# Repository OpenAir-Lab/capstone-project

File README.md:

<h1 align="center">
<<<<<<< HEAD
  <a href="https://github.com/OpenAir-Lab/capstone-project">
    
=======
  <a href="https://github.com/GITHUB_USERNAME/REPO_SLUG">
    
>>>>>>> 1358599 (docs: organized REV A and REV B pcb and schematic files and put them into their relavent folders)
  </a>
</h1>

<div align="center">
  OpenAir Lab – Modular Handheld Radio Development Kit  
  <br />
  <a href="#about"><strong>Explore the project »</strong></a>
  <br /><br />
<<<<<<< HEAD
  <a href="https://github.com/OpenAir-Lab/capstone-project/issues/new?labels=bug&template=01_BUG_REPORT.md&title=bug%3A+">Report a Bug</a>
  ·
  <a href="https://github.com/OpenAir-Lab/capstone-project/issues/new?labels=enhancement&template=02_FEATURE_REQUEST.md&title=feat%3A+">Request a Feature</a>
  ·
  <a href="https://github.com/OpenAir-Lab/capstone-project/issues/new?labels=question&template=04_SUPPORT_QUESTION.md&title=support%3A+">Ask a Question</a>
=======
  <a href="https://github.com/GITHUB_USERNAME/REPO_SLUG/issues/new?labels=bug&template=01_BUG_REPORT.md&title=bug%3A+">Report a Bug</a>
  ·
  <a href="https://github.com/GITHUB_USERNAME/REPO_SLUG/issues/new?labels=enhancement&template=02_FEATURE_REQUEST.md&title=feat%3A+">Request a Feature</a>
  ·
  <a href="https://github.com/GITHUB_USERNAME/REPO_SLUG/issues/new?labels=question&template=04_SUPPORT_QUESTION.md&title=support%3A+">Ask a Question</a>
>>>>>>> 1358599 (docs: organized REV A and REV B pcb and schematic files and put them into their relavent folders)
</div>

<div align="center">

<<<<<<< HEAD

=======

>>>>>>> 1358599 (docs: organized REV A and REV B pcb and schematic files and put them into their relavent folders)

</div>

---

## **About**

OpenAir Lab is an **open-source, modular handheld ham-radio development kit** designed to expose and teach all fundamental subsystems of a portable transceiver. Unlike commercial “black-box” radios, this platform separates RF, MCU, audio, power, and HMI into independent **Modulinos** connected through standardized EYESPI and I²C interfaces.

<<<<<<< HEAD
The system’s core is an **ESP32-WROVER-E** MCU hosting RF control, audio streaming, display driving, and power-management logic. 

Subsystems include:

- **RF modulino:** TI CC1200 sub-GHz transceiver  

- **HMI modulino:** 1.9" ST7789 TFT via EYESPI, keypad, user buttons, rotary encoder  

- **Audio modulino:** ICS-43434 digital MEMS microphone + MAX98357A I²S amplifier 

- **Power modulino:** STUSB4500 USB-PD, BQ25622 charger, fuel gauge  

- **Control plane:** I²C expander for low-rate signals (LEDs, keypad, resets, alerts)

=======
The system’s core is an **ESP32-WROVER-E** MCU hosting RF control, audio streaming, display driving, and power-management logic. Subsystems include:

- **RF modulino:** TI CC1200 sub-GHz transceiver  
- **HMI modulino:** 1.9" ST7789 TFT via EYESPI, keypad, user buttons, rotary encoder  
- **Audio modulino:** ICS-43434 digital MEMS microphone + MAX98357A I²S amplifier  
- **Power modulino:** STUSB4500 USB-PD, BQ25620 charger, fuel gauge  
- **Control plane:** I²C expander for low-rate signals (LEDs, keypad, resets, alerts)

>>>>>>> 1358599 (docs: organized REV A and REV B pcb and schematic files and put them into their relavent folders)
Purpose:  
• Provide a hands-on educational platform for embedded, RF, and systems engineering  
• Enable modular experimentation and rapid firmware iteration  
• Deliver a working open-source handheld radio for expo demonstration  

---

### **Built With**

- **ESP32-WROVER-E** (dual-core 240 MHz, Wi-Fi/BT, PSRAM)
- **CC1200 Sub-GHz RF Transceiver**  
- **Adafruit 1.9" ST7789 TFT Display + EYESPI connector**  
- **ICS-43434 MEMS microphone**  
- **MAX98357A I²S amplifier**  
- **STUSB4500 USB-PD controller**  
- **BQ25620 battery management IC**  
- **I²C GPIO Expander (TCA9539/MCP23017)**  
- **FreeRTOS-style firmware architecture** (timers, ISRs, tasks)

---

## **Getting Started**

### **Prerequisites**

The project requires:

- ESP32 toolchain (ESP-IDF or PlatformIO/Arduino)
- EYESPI breakout for the TFT display (18-pin FPC)
- Access to I²C and SPI buses for CC1200, audio, and PD controller  
- 3.3 V power supply capable of ≥500 mA for ESP32-WROVER-E  

### **Installation**

1. Clone the repository  
2. Open the firmware directory in ESP-IDF or PlatformIO  
3. Connect the MCU modulino to UART (use BOOT/EN buttons on custom boards)  
4. Build and flash the firmware  
5. Connect modulinos via EYESPI and I²C cables  

---

## **Usage**

Firmware operates through **interrupt-driven inputs**, **FreeRTOS tasks**, and **timers**:

- Keypad, encoder, and PTT interrupts update application state  
- CC1200 provides frequency control, RX/TX switching, and RSSI sampling  
- TFT displays live frequency, signal strength, battery state, settings  
- Tasks handle display refresh, PTT timeout, and periodic battery polling  
- Audio subsystem processes microphone data and sends I²S audio to amplifier  

---

## **Roadmap**

See open issues:  
<<<<<<< HEAD
https://github.com/OpenAir-Lab/capstone-project/issues
=======
https://github.com/GITHUB_USERNAME/REPO_SLUG/issues
>>>>>>> 1358599 (docs: organized REV A and REV B pcb and schematic files and put them into their relavent folders)

Current priorities:

- Finalize pin mapping across all modulinos  
- Complete MCU subsystem schematic in KiCad  
- Implement full FreeRTOS task architecture  
- Bring-up and test Rev A PCB  
- Assemble proof-of-concept handheld radio for expo  

---

## **Support**

Contact the maintainers via:

- GitHub issues (for questions):  
<<<<<<< HEAD
  https://github.com/OpenAir-Lab/capstone-project/issues/new?labels=question  
=======
  https://github.com/GITHUB_USERNAME/REPO_SLUG/issues/new?labels=question  
>>>>>>> 1358599 (docs: organized REV A and REV B pcb and schematic files and put them into their relavent folders)
- Maintainer contact info on GitHub profile  

---

## **Project Assistance**

If you want to support the project:

- Star the repo ⭐  
- Share the project  
- Contribute hardware, firmware, or documentation improvements  

---

## **Contributing**

Contributions are welcome!  
<<<<<<< HEAD
Please review `Documentation/Contributing.md` before submitting a pull request.
=======
Please review `docs/CONTRIBUTING.md` before submitting a pull request.
>>>>>>> 1358599 (docs: organized REV A and REV B pcb and schematic files and put them into their relavent folders)

---

## **Authors & Contributors**

Project created and maintained by the OpenAir Lab MCU & Systems Integration Team.  
Full contributor list:  
<<<<<<< HEAD
https://github.com/OpenAir-Lab/capstone-project/contributors
=======
https://github.com/GITHUB_USERNAME/REPO_SLUG/contributors
>>>>>>> 1358599 (docs: organized REV A and REV B pcb and schematic files and put them into their relavent folders)

---

## **Security**

Provided “as is” with no warranty.  
See `docs/SECURITY.md` for disclosure instructions.

---

## **License**

Licensed under the **MIT License**.  
See `LICENSE` for details.

---

## **Acknowledgements**

This project uses or references:

- **Espressif – ESP32-WROVER-E Datasheet & Technical Reference Manual**  
- **Adafruit – ST7789 TFT & EYESPI Documentation**  
- **Texas Instruments – CC1200 RF Transceiver**  
- **STMicroelectronics – STUSB4500 USB-PD Controller**  
- **TDK/Knowles – ICS-43434 MEMS Microphone**  
- **MAX98357A I²S Amplifier Datasheet**

We also acknowledge the design documentation for the OpenAir Lab subsystem interface and pin mapping.

---

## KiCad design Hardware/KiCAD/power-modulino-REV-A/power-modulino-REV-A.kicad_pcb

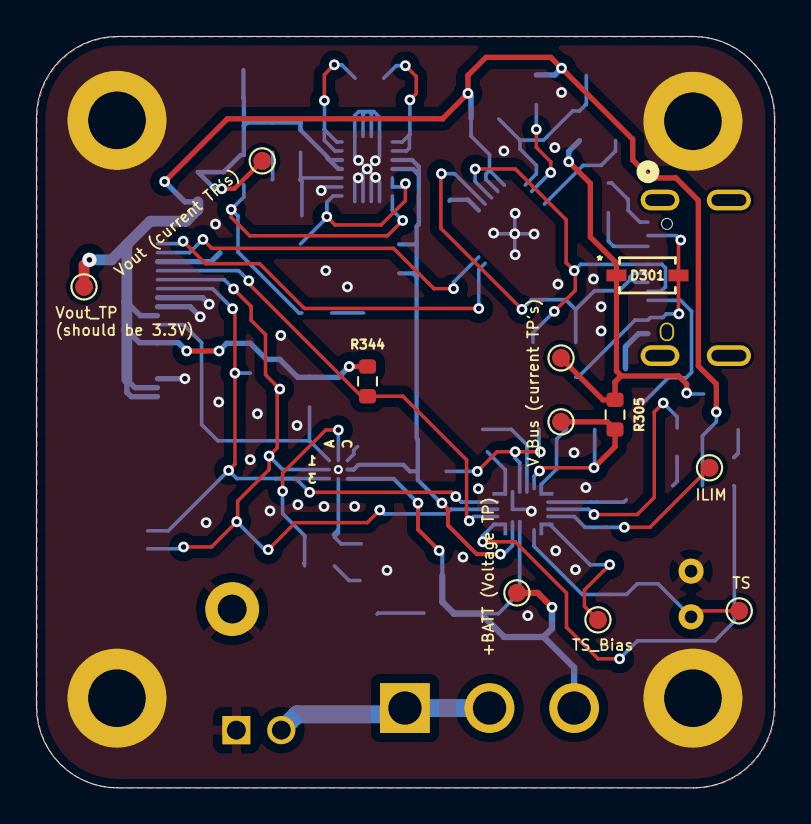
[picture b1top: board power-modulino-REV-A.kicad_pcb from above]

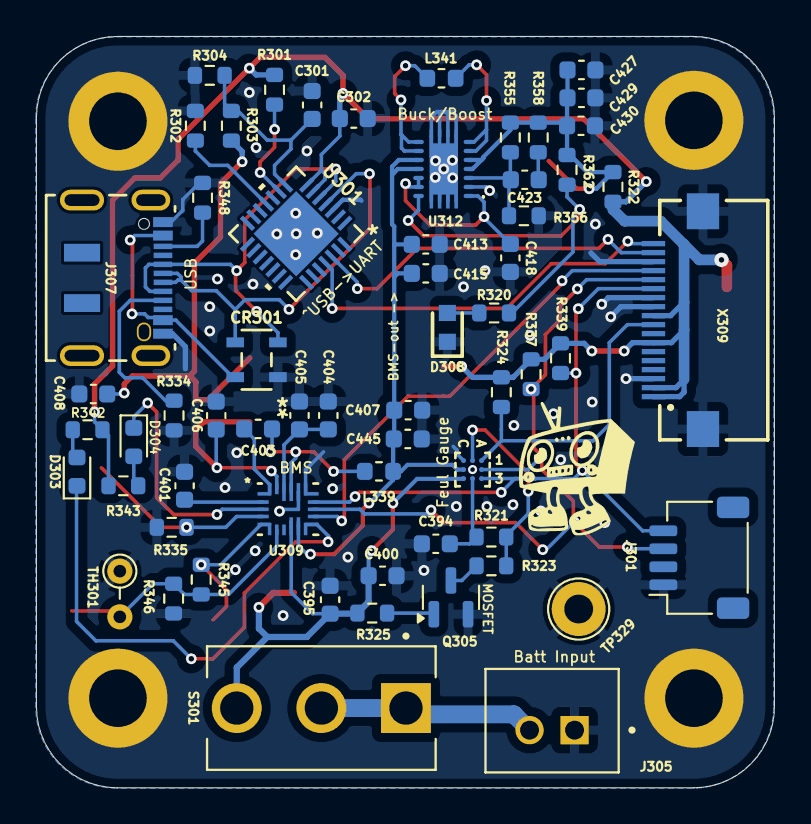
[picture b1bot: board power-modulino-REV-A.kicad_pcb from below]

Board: 2 copper layers, 41.0 x 41.7 mm, 76 parts (65 on the bottom side), 44 nets.

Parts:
C301, C395, C406, C445: 1uF; C_0603_1608Metric
C302, C405: 10uF; C_0603_1608Metric
C394: 2.2uF; C_0603_1608Metric
C400: 10uf; C_0603_1608Metric
C401: 4.7uF; C_0603_1608Metric
C403: 47nF; C_0603_1608Metric
C404: 0.1uF; C_0603_1608Metric
C407: 20uF; C_0603_1608Metric
C408: 4.7u; C_0603_1608Metric
C413, C415: 10u; C_0603_1608Metric
C418: 100n; C_0603_1608Metric
C423: C; C_0603_1608Metric
C427, C429, C430: 22u; C_0603_1608Metric
CR301: SP0503BAHTG; TVS-SP05_LTF
D301: 1N4148WT; 1N5819HW-7-F_DIO
D303, D304: LED; LED_0603_1608Metric
D308: LED; LTST-C190KRKT
H305, H306, H307, H308: MountHole; MountingHole_3.2mm_M3_ISO14580_Pad
J301: Stemma QT; JST_SH_SM04B-SRSS-TB_1x04-1MP_P1.00mm_Horizontal
J305: B2B-XH-A; JST_B2B-XH-A
J307: DX07S016JA1R1500; CONN12_016JA1R1500_JAE
L339: 1uH; L_0603_1608Metric
L341: L; L_0603_1608Metric
Q305: 2N7002; SOT-23
R301: 1K; R_0603_1608Metric
R302, R323, R324, R337, R339, R342, R343, R344: 10k; R_0603_1608Metric
R303: 22.1K; R_0603_1608Metric
R304: 47.5K; R_0603_1608Metric
R305: 0.01; R_0603_1608Metric
R320: 1k; R_0603_1608Metric
R321: 1.8M; R_0603_1608Metric
R322: 0; R_0603_1608Metric
R325: tbd; R_0603_1608Metric
R334, R348: 5.1k; R_0603_1608Metric
R335: TBD; R_0603_1608Metric
R345, R346, R355, R356, R358, R362: R; R_0603_1608Metric
S301: 100SP1T1B4M2QE; SW_100SP1T1B4M2QE
TH301: Thermistor_NTC; R_Axial_DIN0204_L3.6mm_D1.6mm_P2.54mm_Vertical
TP323, TP324, TP326, TP327, TP334, TP335, TP337, TP338: TestPoint; TestPoint_Pad_D1.0mm
TP329: TestPoint; TestPoint_Loop_D2.60mm_Drill1.6mm_Beaded
U301: CP2102N-A02-GQFN28; QFN28_5X5_SIL
U308: BQ27427YZFR; DSBGA9-YZF_TEX
U309: BQ25622RYKR; WQFN-HR18__RYK_TEX
U312: TPS63020QDSJRQ1; TPS63020DSJR
X309: EYESPI; Adafruit EYESPI FPC Connector

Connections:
+3.3V: C302.2, R301.2, R322.1, R324.1, R337.2, R339.2, R342.2, R343.2, R344.2, TP324.1, U301.6 (VDD), U301.7 (VREGIN), X309.1, X309.2, X309.7, X309.10
+BATT: C395.1, C400.1, R325.2, S301.3, TP334.1, U308.C3 (BAT), U309.8 (BAT)
/Power Subsystem/*INT: R344.1, U309.11 (*INT), X309.15
/Power Subsystem/*PG: D304.1 (K), U309.3 (*PG)
/Power Subsystem/BMS_out: C407.2, C413.1, C415.1, C445.2, L339.2, U308.C2 (SRX), U309.9 (SYS), U312.10 (VIN_1), U312.11 (VIN_2)
/Power Subsystem/D+: CR301.3, J307.6 (D+), J307.7 (D+__1), U301.4 (D+)
/Power Subsystem/D-: CR301.2, J307.5 (D-), J307.8 (D-__1), U301.5 (D-)
/Power Subsystem/ILIM: R335.2, TP337.1, U309.4 (ILIM)
/Power Subsystem/RXD: U301.25 (RXD), X309.18
/Power Subsystem/SCL: J301.4, R339.1, U308.A3 (SCL), U309.13 (SCL), X309.13
/Power Subsystem/SDA: J301.3, R337.1, U308.A2 (SDA), U309.12 (SDA), X309.14
/Power Subsystem/STAT: D303.1 (K), U309.10 (STAT)
/Power Subsystem/TS: R345.2, R346.1, TH301.2, TP338.1, U309.6 (TS)
/Power Subsystem/TS_BIAS: R345.1, TP335.1, U309.5 (TS_BIAS)
/Power Subsystem/TXD: U301.26 (TXD), X309.17
/Power Subsystem/VDD: C394.1, R321.2, U308.B3 (VDD)
/Power Subsystem/~BAT_INT: R324.2, U308.A1 (GPOUT), X309.9
GND: C301.1, C302.1, C394.2, C395.2, C400.2, C401.1, C404.1, C405.1, C406.1, C407.1, C408.2, C413.2, C415.2, C418.2, C427.2, C429.2, C430.2, C445.1, CR301.1, D308.1 (K), H305.1, H306.1, H307.1, H308.1, J301.1, J305.1, J307.1 (GND), J307.12 (GND__1), Q305.2 (S), R302.2, R304.1, R334.2, R335.1, R346.2, R348.2, R356.1, TH301.1, TP329.1, U301.3 (GND), U301.29 (GND), U308.B2 (VSS), U308.C1 (VSS), U309.14 (*CE), U309.15 (GND), U312.2 (GND), U312.15 (PGND_1), U312.16 (GND), U312.17 (GND), U312.18 (GND), U312.19 (GND), U312.20 (GND), U312.21 (GND), U312.22 (GND), U312.23 (GND), X309.3, X309.11, X309.12, X309.16, X309.Z1, X309.Z2
unnamed: C423.1, R358.1
unnamed: CR301.4, D301.2 (A), J307.2 (VBUS), J307.11 (VBUS__1)
unnamed: D303.2 (A), R342.1
unnamed: D304.2 (A), R343.1
unnamed: D308.2 (A), R320.2
unnamed: J305.2, S301.1, S301.2
unnamed: J307.3 (CC1), R348.1
unnamed: J307.9 (CC2), R334.1
unnamed: Q305.3 (D), R323.1
unnamed: Q305.1 (G), R325.1
unnamed: R301.1, U301.9 (RSTb)
unnamed: R302.1, U301.11 (SUSPENDb)
unnamed: C301.2, R303.2, R304.2, U301.8 (VBUS)
unnamed: R321.1, R323.2, U308.B1 (BIN)
unnamed: C403.2, U309.1 (BTST)
unnamed: C404.2, C405.2, U309.17 (PMID)
unnamed: C401.2, U309.2 (REGN)
unnamed: C403.1, L339.1, U309.16 (SW)
unnamed: C406.2, R305.2, TP326.1, U309.18 (VBUS)
unnamed: C418.1, U312.1 (VINA), U312.12 (EN), U312.13 (PS/SYNC)
unnamed: C423.2, R355.1, R356.2, U312.3 (FB)
unnamed: L341.1, U312.8 (L1_1), U312.9 (L1_2)
unnamed: L341.2, U312.6 (L2_1), U312.7 (L2_2)
unnamed: R320.1, R362.1, U312.14 (PG)
unnamed: C427.1, C429.1, C430.1, R322.2, R355.2, R358.2, R362.2, TP323.1, U312.4 (VOUT_1), U312.5 (VOUT_2)
VBUS: C408.1, D301.1 (K), R303.1, R305.1, TP327.1

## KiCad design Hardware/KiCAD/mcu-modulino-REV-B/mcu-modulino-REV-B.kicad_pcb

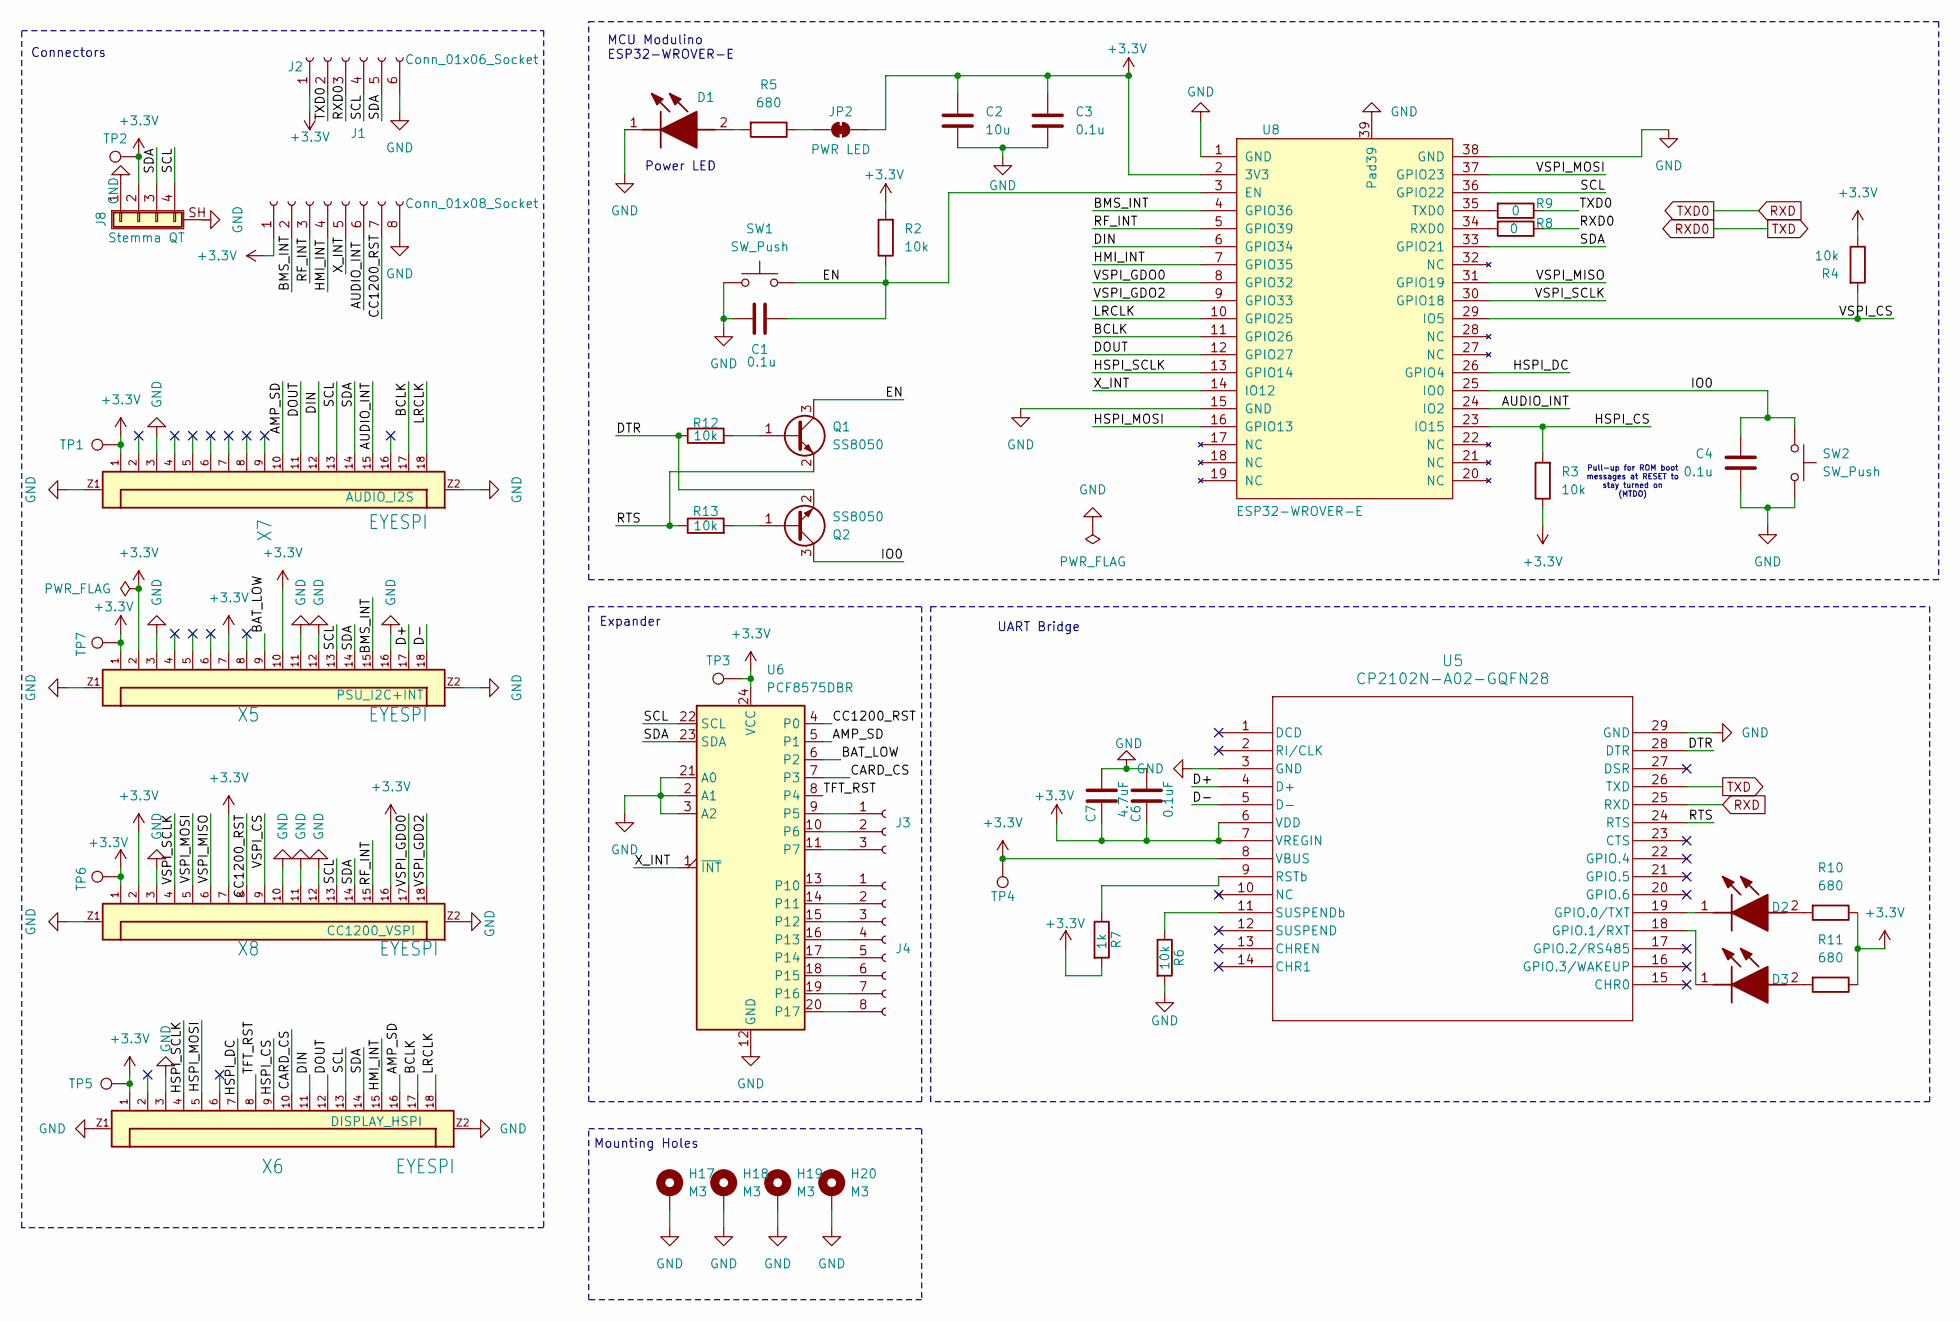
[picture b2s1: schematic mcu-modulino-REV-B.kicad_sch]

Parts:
C1, C3, C4: 0.1u; C_0603_1608Metric
C2: 10u; C_0603_1608Metric
C6: 0.1uF; C_0603_1608Metric
C7: 4.7uF; C_0603_1608Metric
D1: LTST-C190KRKT; LED_0603_1608Metric; Mouser Part Number 859-LTST-C190KRKT
D2, D3: LTST-C191GKT; Mouser Part Number 859-LTST-C191GKT
H17, H18, H19, H20: M3; MountingHole_3.2mm_M3_ISO14580_Pad
J1: Conn_01x08_Socket; PinSocket_1x08_P2.54mm_Vertical
J2: Conn_01x06_Socket; PinHeader_1x06_P1.00mm_Vertical
J3: Conn_01x03_Socket; PinSocket_1x03_P1.27mm_Vertical
J4: Conn_01x08_Socket; PinSocket_1x08_P1.27mm_Vertical
J8: Stemma QT; JST_SH_SM04B-SRSS-TB_1x04-1MP_P1.00mm_Horizontal
JP2: PWR LED; SolderJumper-2_P1.3mm_Bridged_RoundedPad1.0x1.5mm
Q1, Q2: SS8050; SOT-23
R2, R3, R4, R6, R12, R13: 10k; R_0603_1608Metric
R5, R10, R11: 680; R_0603_1608Metric
R7: 1k; R_0603_1608Metric
R8, R9: 0; R_0603_1608Metric
SW1, SW2: SW_Push; SW_SPST_EVQP2_MiddlePushTravel_H2.5mm
TP1, TP2, TP3, TP4, TP5, TP6, TP7: TestPoint; TestPoint_Pad_D1.0mm
U5: CP2102N-A02-GQFN28; QFN28_5X5_SIL
U6: PCF8575DBR; SSOP-24_5.3x8.2mm_P0.65mm
U8: ESP32-WROVER-E; ESP32-WROVER-IE
X5, X6, X7, X8: EYESPI; Adafruit EYESPI FPC Connector

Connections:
+3.3V: C2.1, C3.1, C6.2, C7.2, J2.1, J8.2, JP2.2 (B), R2.2, R3.1, R4.1, R7.2, R10.1, R11.1, TP1.1, TP2.1, TP3.1, TP4.1, TP5.1, TP6.1, TP7.1, U5.6 (VDD), U5.7 (VREGIN), U5.8 (VBUS), U6.24 (VCC), U8.2 (3V3), X5.1, X5.2, X5.7, X5.10, X6.1, X7.1, X8.1, X8.2, X8.7, X8.16
/AMP_SD: U6.5 (P1), X6.16, X7.10
/AUDIO_INT: J1.6, U8.24 (IO2), X7.15
/BAT_LOW: U6.6 (P2), X5.9
/BCLK: U8.11 (GPIO26), X6.17, X7.17
/BMS_INT: U8.4 (GPIO36), X5.15
/CARD_CS: U6.7 (P3), X6.10
/CC1200_RST: U6.4 (P0), X8.8
/D+: U5.4 (D+), X5.17
/D-: U5.5 (D-), X5.18
/DIN: U8.6 (GPIO34), X6.11, X7.12
/DOUT: U8.12 (GPIO27), X6.12, X7.11
/DTR: Q2.2 (E), R12.1, U5.28 (DTR)
/EN: C1.2, Q1.3 (C), R2.1, SW1.2, U8.3 (EN)
/HMI_INT: U8.7 (GPIO35), X6.15
/HSPI_CS: R3.2, U8.23 (IO15), X6.9
/HSPI_DC: U8.26 (GPIO4), X6.7
/HSPI_MOSI: U8.16 (GPIO13), X6.5
/HSPI_SCLK: U8.13 (GPIO14), X6.4
/IO0: C4.1, Q2.3 (C), SW2.1, U8.25 (IO0)
/LRCLK: U8.10 (GPIO25), X6.18, X7.18
/RF_INT: U8.5 (GPIO39), X8.15
/RTS: Q1.2 (E), R13.1, U5.24 (RTS)
/SCL: J2.4, J8.4, U6.22 (SCL), U8.36 (GPIO22), X5.13, X6.13, X7.13, X8.13
/SDA: J2.5, J8.3, U6.23 (SDA), U8.33 (GPIO21), X5.14, X6.14, X7.14, X8.14
/TFT_RST: U6.8 (P4), X6.8
/VSPI_CS: R4.2, U8.29 (IO5), X8.9
/VSPI_GDO0: U8.8 (GPIO32), X8.17
/VSPI_GDO2: U8.9 (GPIO33), X8.18
/VSPI_MISO: U8.31 (GPIO19), X8.6
/VSPI_MOSI: U8.37 (GPIO23), X8.5
/VSPI_SCLK: U8.30 (GPIO18), X8.4
/X_INT: J1.5, U6.1 (~INT), U8.14 (IO12)
GND: C1.1, C2.2, C3.2, C4.2, C6.1, C7.1, D1.1 (K), H18.1, H20.1, J2.6, J8.1, J8.SH (Shield), R6.2, SW1.1, SW2.2, U5.3 (GND), U5.29 (GND), U6.2 (A1), U6.3 (A2), U6.12 (GND), U6.21 (A0), U8.1 (GND), U8.15 (GND), U8.38 (GND), U8.39 (Pad39), X5.3, X5.11, X5.12, X5.16, X5.Z1, X5.Z2, X6.3, X6.Z1, X6.Z2, X7.3, X7.Z1, X7.Z2, X8.3, X8.10, X8.11, X8.12, X8.Z1, X8.Z2
unnamed: D1.2 (A), R5.2
unnamed: D2.2 (A), R10.2
unnamed: D2.1 (K), U5.19 (GPIO.0/TXT)
unnamed: D3.2 (A), R11.2
unnamed: D3.1 (K), U5.18 (GPIO.1/RXT)
unnamed: J3.1, U6.9 (P5)
unnamed: J3.2, U6.10 (P6)
unnamed: J3.3, U6.11 (P7)
unnamed: J4.1, U6.13 (P10)
unnamed: J4.2, U6.14 (P11)
unnamed: J4.3, U6.15 (P12)
unnamed: J4.4, U6.16 (P13)
unnamed: J4.5, U6.17 (P14)
unnamed: J4.6, U6.18 (P15)
unnamed: J4.7, U6.19 (P16)
unnamed: J4.8, U6.20 (P17)
unnamed: JP2.1 (A), R5.1
unnamed: Q1.1 (B), R12.2
unnamed: Q2.1 (B), R13.2
unnamed: R7.1, U5.9 (RSTb)
unnamed: R6.1, U5.11 (SUSPENDb)
unnamed: R8.2, U8.34 (RXD0)
unnamed: R9.2, U8.35 (TXD0)
RXD: J2.2, R9.1, U5.25 (RXD)
RXD0: J2.3, R8.1, U5.26 (TXD)

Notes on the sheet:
UART Bridge
Pull-up for ROM boot messages at RESET to stay turned on (MTDO)
Power LED
Connectors
MCU Modulino ESP32-WROVER-E
Expander
Mounting Holes

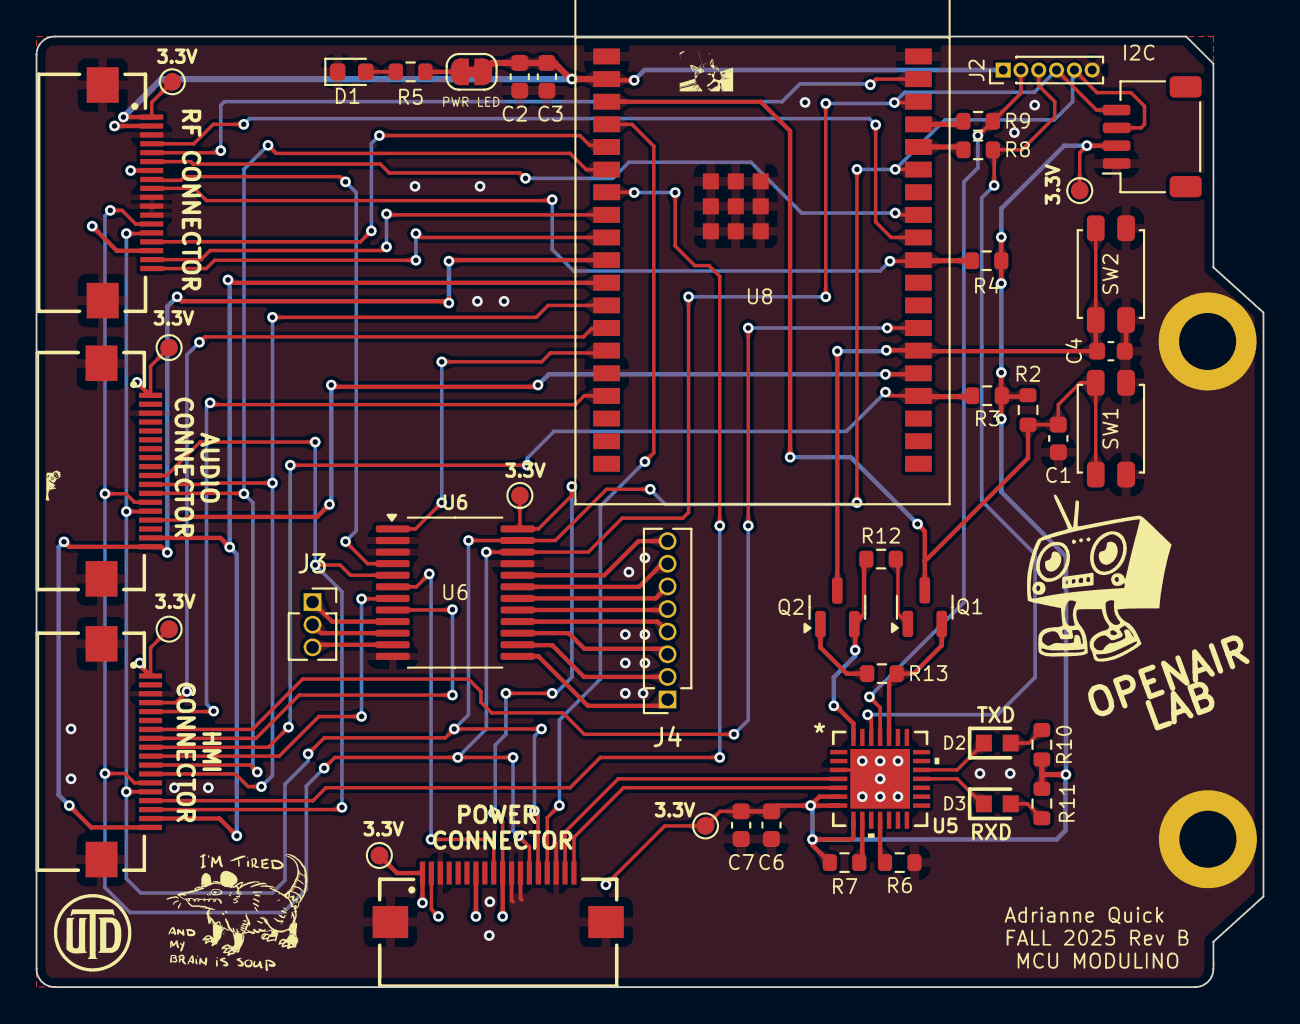
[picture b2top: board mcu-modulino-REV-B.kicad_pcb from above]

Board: 4 copper layers, 68.9 x 53.3 mm, 46 parts (0 on the bottom side), 59 nets.

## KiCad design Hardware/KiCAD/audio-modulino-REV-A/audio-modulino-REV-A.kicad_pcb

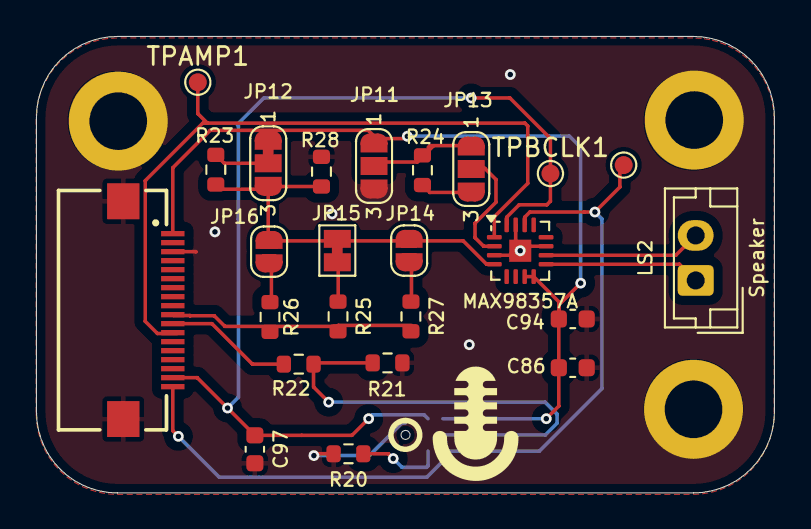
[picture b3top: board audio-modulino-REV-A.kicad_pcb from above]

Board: 2 copper layers, 41.0 x 25.4 mm, 28 parts (1 on the bottom side), 19 nets.

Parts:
C86: 1uF; C_0603_1608Metric
C94: 0.1uF; C_0603_1608Metric
C97: 22pF; C_0603_1608Metric
H13, H15, H16: M3; MountingHole_3.2mm_M3_ISO14580_Pad
JP11: GAIN_{LOGIC}; SolderJumper-3_P1.3mm_Open_RoundedPad1.0x1.5mm_NumberLabels
JP12: Driver; SolderJumper-3_P1.3mm_Bridged12_RoundedPad1.0x1.5mm_NumberL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
JP13: GAIN_{R}; SolderJumper-3_P1.3mm_Open_RoundedPad1.0x1.5mm_NumberLabels
JP14: CH_LEFT; SolderJumper-2_P1.3mm_Open_RoundedPad1.0x1.5mm
JP15: CH_MONO_MIX; SolderJumper-2_P1.3mm_Bridged_Pad1.0x1.5mm
JP16: CH_RIGHT; SolderJumper-2_P1.3mm_Open_RoundedPad1.0x1.5mm
LS2: Speaker; JST_EH_B2B-EH-A_1x02_P2.50mm_Vertical
MK2: ICS-43434; InvenSense_ICS-43434-6_3.5x2.65mm
R20, R21: 47k; R_0603_1608Metric
R22: 68; R_0603_1608Metric
R23, R27: 2k; R_0603_1608Metric
R24: 100k 5%; R_0603_1608Metric
R25: 634k; R_0603_1608Metric
R26: 330k; R_0603_1608Metric
R28: 100k; R_0603_1608Metric
TPAMP1: TestPoint_Pad_D1.0mm
TPBCLK1: TestPoint_Pad_D1.0mm
TPLRCLK1: TestPoint_Pad_D1.0mm
U7: MAX98357A; TQFN-16-1EP_3x3mm_P0.5mm_EP1.23x1.23mm
X2: EYESPI; Adafruit EYESPI FPC Connector

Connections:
+3.3V: C86.1, C94.1, JP11.1 (A), JP12.1 (A), MK2.5 (VDD), U7.7 (VDD), U7.8 (VDD), X2.1
/AMP_DIN: TPAMP1.1, U7.1 (DIN), X2.12
/Audio Subsystem/GAIN_SLOT: JP13.2 (C), U7.2 (GAIN_SLOT)
/Audio Subsystem/~SD_MODE: JP12.3 (B), JP14.2 (B), JP15.2 (B), JP16.2 (B), R23.2, R28.2, U7.4 (~SD_MODE)
/BCLK: C97.1, MK2.4 (SCK), TPBCLK1.1, U7.16 (BCLK), X2.17
/LRCLK: MK2.1 (WS), TPLRCLK1.1, U7.14 (LRCLK), X2.18
/MIC_DOUT: R22.2, X2.11
/~AMP_SD: R25.2, R26.1, R27.2, X2.10
GND: C86.2, C94.2, C97.2, H13.1, H15.1, H16.1, JP11.3 (B), MK2.3 (GND), R20.2, R21.2, R28.1, U7.3 (GND), U7.11 (GND), U7.15 (GND), U7.17 (PAD), X2.3, X2.Z1, X2.Z2
unnamed: JP11.2 (C), JP13.1 (A), R24.1
unnamed: JP12.2 (C), R23.1
unnamed: JP13.3 (B), R24.2
unnamed: JP14.1 (A), R27.1
unnamed: JP15.1 (A), R25.1
unnamed: JP16.1 (A), R26.2
unnamed: MK2.2 (LR), R20.1
unnamed: MK2.6 (SD), R21.1, R22.1
unnamed: LS2.2, U7.10 (OUTN)
unnamed: LS2.1, U7.9 (OUTP)

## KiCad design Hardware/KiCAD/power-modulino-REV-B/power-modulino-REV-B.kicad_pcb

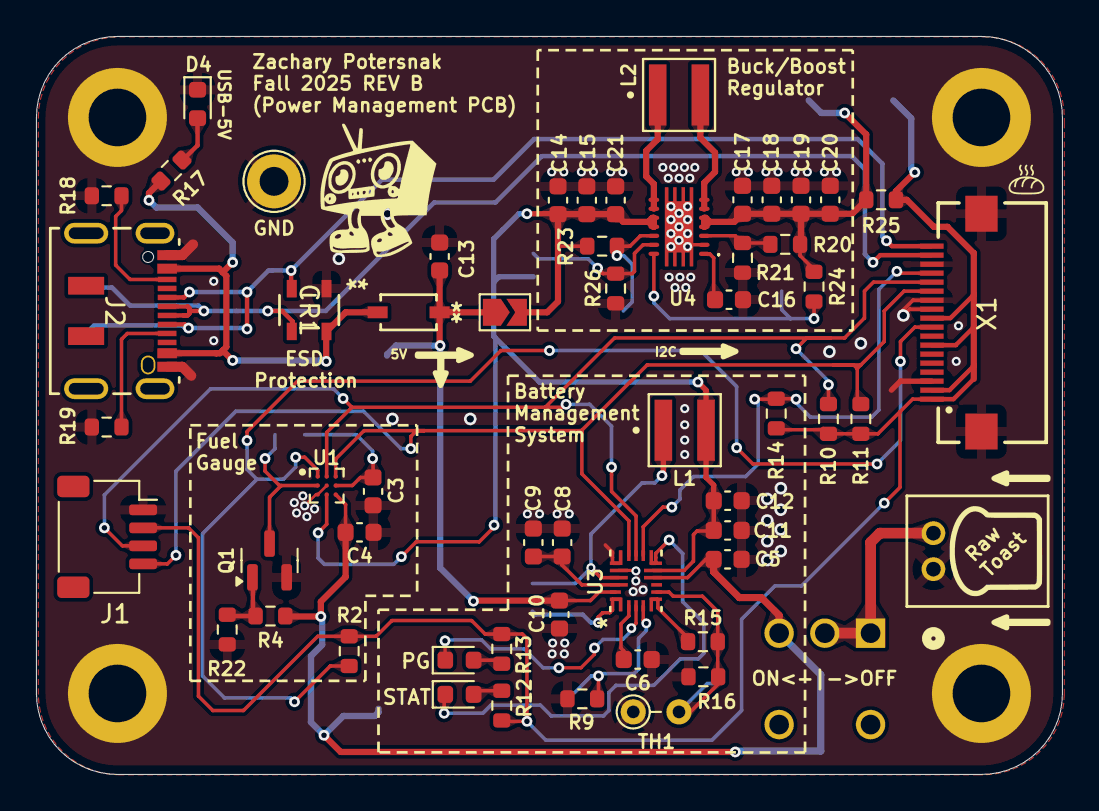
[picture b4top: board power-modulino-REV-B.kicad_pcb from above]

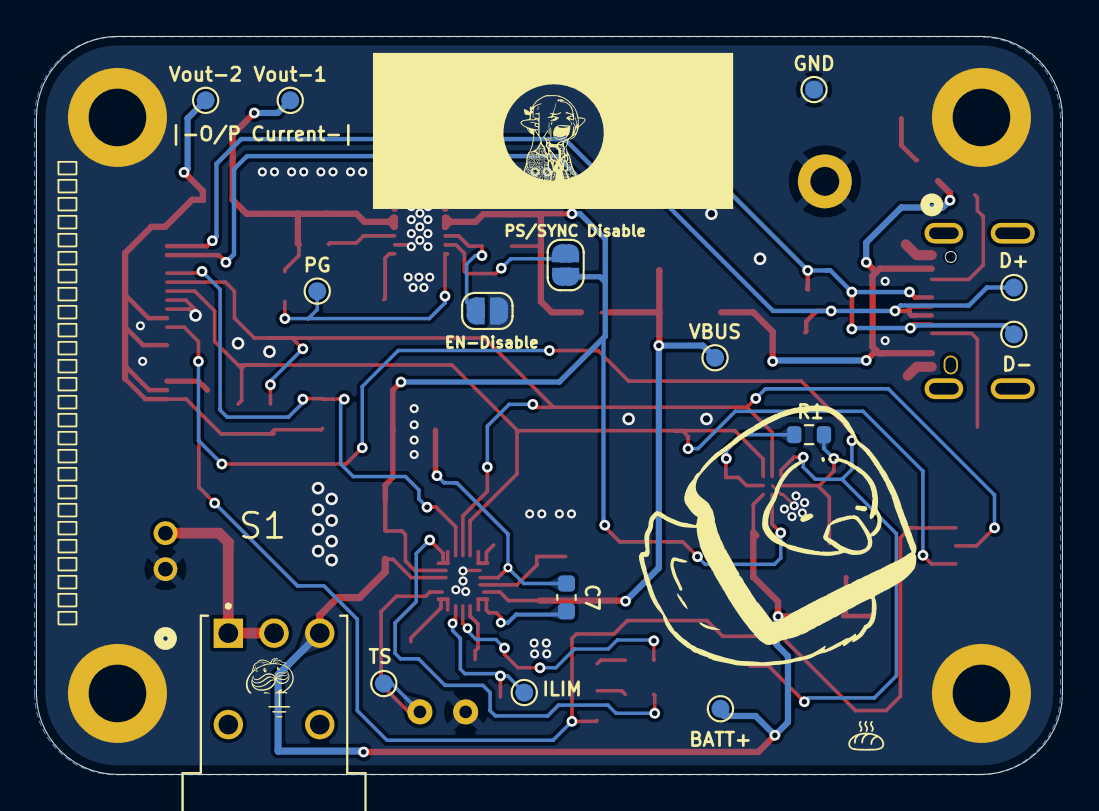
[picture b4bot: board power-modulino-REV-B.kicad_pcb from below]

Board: 2 copper layers, 57.0 x 41.0 mm, 75 parts (15 on the bottom side), 38 nets.

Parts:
BATT+: TestPoint; TestPoint_Pad_D1.0mm
C3: 2.2uF; C_0603_1608Metric
C4, C10, C12: 1uF; C_0603_1608Metric
C5: 10uf; C_0603_1608Metric
C6: 4.7uF; C_0603_1608Metric
C7: 47nF; C_0603_1608Metric
C8: 0.1uF; C_0603_1608Metric
C9: 10uF; C_0603_1608Metric
C11: 20uF; C_0603_1608Metric
C13: 4.7u; C_0603_1608Metric
C14, C15, C18, C19, C20: 22u; C_0603_1608Metric
C16: 100n; C_0603_1608Metric
C17, C21: 2.2u; C_0603_1608Metric
CR1: SP0503BAHTG; TVS-SP05_LTF
D3: 1N4148WT; 1N5819HW-7-F_DIO
D4: LED; LED_0603_1608Metric
D+: TestPoint; TestPoint_Pad_D1.0mm
D-: TestPoint; TestPoint_Pad_D1.0mm
GND: TestPoint; TestPoint_Loop_D2.60mm_Drill1.6mm_Beaded
GND#2: TestPoint; TestPoint_Pad_D1.0mm
H1, H2, H3, H4: MountHole; MountingHole_3.2mm_M3_ISO14580_Pad
ILIM: TestPoint; TestPoint_Pad_D1.0mm
J1: Stemma QT; JST_SH_SM04B-SRSS-TB_1x04-1MP_P1.00mm_Horizontal
J2: DX07S016JA1R1500; CONN12_016JA1R1500_JAE
J3: S2B-PH-K-SLFSN; CONN_S2B-PH-K-S_JST
JP1: SolderJumper_2_Open; SolderJumper-2_P1.3mm_Open_TrianglePad1.0x1.5mm
JP2, JP3: SolderJumper_2_Open; SolderJumper-2_P1.3mm_Open_RoundedPad1.0x1.5mm
L1: 2.2uH; IND_XFL4020-222MEC
L2: 1.5u; IND_XFL4020-222MEC
PG: LED; LED_0603_1608Metric
PG#2: TestPoint; TestPoint_Pad_D1.0mm
Q1: 2N7002; SOT-23
R1: 1.8M; R_0603_1608Metric
R2, R10, R11, R14: 10k; R_0603_1608Metric
R4: 100; R_0603_1608Metric
R9: 1.6k; R_0603_1608Metric
R12, R13: 2.2k; R_0603_1608Metric
R15, R18, R19: 5.1k; R_0603_1608Metric
R16: 30k; R_0603_1608Metric
R17: 1.2K; R_0603_1608Metric
R20, R23, R24, R26: 1M; R_0603_1608Metric
R21: 180k; R_0603_1608Metric
R22: 100K; R_0603_1608Metric
R25: 0; R_0603_1608Metric
S1: 500ASSP1M6QE; SW_500ASSP1M6QE
STAT: LED; LED_0603_1608Metric
TH1: Thermistor_NTC; R_Axial_DIN0204_L3.6mm_D1.6mm_P2.54mm_Vertical
TS: TestPoint; TestPoint_Pad_D1.0mm
U1: BQ27427YZFR; IC_BQ27427YZFR
U3: BQ25622RYKR; WQFN-HR18__RYK_TEX
U4: TPS63020QDSJRQ1; TPS63020DSJR
VBUS: TestPoint; TestPoint_Pad_D1.0mm
Vout-1, Vout-2: TestPoint; TestPoint_Pad_D1.0mm
X1: EYESPI; Adafruit EYESPI FPC Connector

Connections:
+3.3V: J1.2, R2.1, R10.2, R11.2, R12.2, R13.2, R14.2, R25.1, Vout-2.1, X1.1, X1.2, X1.7, X1.10
+5V: C11.2, C12.2, C14.1, C15.1, C21.1, JP1.2 (B), JP3.2 (B), L1.2, R23.1, U1.C2 (SRX), U3.9 (SYS), U4.10 (VIN_1), U4.11 (VIN_2)
+BATT: BATT+.1, C4.1, C5.1, R4.2, S1.3, U1.C3 (BAT), U3.8 (BAT)
/Power Subsystem/*INT: R14.1, U3.11 (*INT), X1.15
/Power Subsystem/*PG: PG.1 (K), U3.3 (*PG)
/Power Subsystem/BAT_LOW: R2.2, U1.A1 (GPOUT), X1.9
/Power Subsystem/D+: CR1.3, D+.1, J2.6 (D+), J2.7 (D+__1), X1.17
/Power Subsystem/D-: CR1.2, D-.1, J2.5 (D-), J2.8 (D-__1), X1.18
/Power Subsystem/ILIM: ILIM.1, R9.2, U3.4 (ILIM)
/Power Subsystem/Regulators/EN: JP2.1 (A), R23.2, U4.12 (EN)
/Power Subsystem/Regulators/PS/SYNC: JP3.1 (A), R26.2, U4.13 (PS/SYNC)
/Power Subsystem/SCL: J1.4, R11.1, U1.A3 (SCL), U3.13 (SCL), X1.13
/Power Subsystem/SDA: J1.3, R10.1, U1.A2 (SDA), U3.12 (SDA), X1.14
/Power Subsystem/STAT: STAT.1 (K), U3.10 (STAT)
/Power Subsystem/TS: R15.2, R16.1, TH1.2, TS.1, U3.6 (TS)
/Power Subsystem/TS_BIAS: R15.1, U3.5 (TS_BIAS)
/Power Subsystem/VDD: C3.1, R1.2, U1.B3 (VDD)
GND: C3.2, C4.2, C5.2, C6.1, C8.1, C9.1, C10.1, C11.1, C12.1, C13.2, C14.2, C15.2, C16.2, C17.2, C18.2, C19.2, C20.2, C21.2, CR1.1, D4.1 (K), GND.1, GND#2.1, H1.1, H2.1, H3.1, H4.1, J1.1, J2.1 (GND), J2.12 (GND__1), J3.1, JP2.2 (B), Q1.2 (S), R9.1, R16.2, R18.2, R19.2, R21.1, R22.2, R26.1, TH1.1, U1.B2 (VSS), U1.C1 (VSS), U3.14 (*CE), U3.15 (GND), U4.2 (GND), U4.15 (PGND_1), X1.3, X1.11, X1.12, X1.16, X1.Z1, X1.Z2
unnamed: R12.1, STAT.2 (A)
unnamed: PG.2 (A), R13.1
unnamed: CR1.4, D3.2 (A), J2.2 (VBUS), J2.11 (VBUS__1), R17.1
unnamed: D4.2 (A), R17.2
unnamed: J2.3 (CC1), R18.1
unnamed: J2.9 (CC2), R19.1
unnamed: J3.2, S1.1, S1.2
unnamed: Q1.3 (D), R1.1, U1.B1 (BIN)
unnamed: Q1.1 (G), R4.1, R22.1
unnamed: C7.2, U3.1 (BTST)
unnamed: C8.2, C9.2, U3.17 (PMID)
unnamed: C6.2, U3.2 (REGN)
unnamed: C7.1, L1.1, U3.16 (SW)
unnamed: R20.1, R21.2, U4.3 (FB)
unnamed: L2.1, U4.8 (L1_1), U4.9 (L1_2)
unnamed: L2.2, U4.6 (L2_1), U4.7 (L2_2)
unnamed: PG#2.1, R24.1, U4.14 (PG)
unnamed: C16.1, U4.1 (VINA)
unnamed: C17.1, C18.1, C19.1, C20.1, R20.2, R24.2, R25.2, U4.4 (VOUT_1), U4.5 (VOUT_2), Vout-1.1
VBUS: C10.2, C13.1, D3.1 (K), JP1.1 (A), U3.18 (VBUS), VBUS.1

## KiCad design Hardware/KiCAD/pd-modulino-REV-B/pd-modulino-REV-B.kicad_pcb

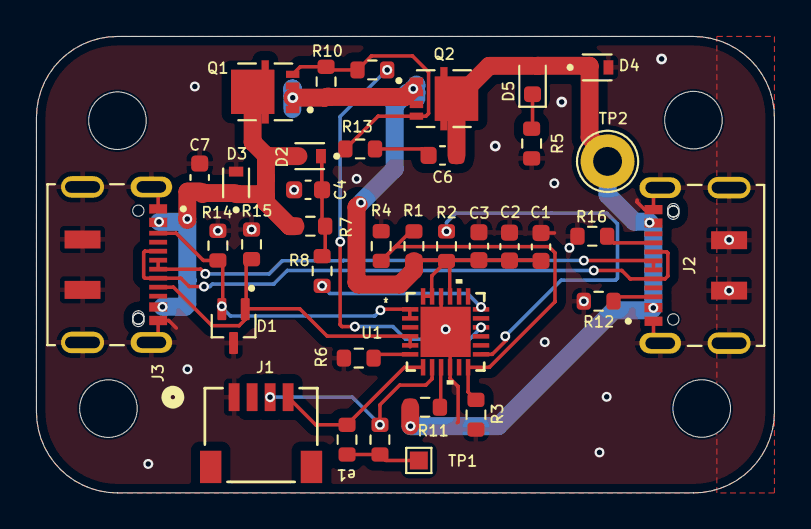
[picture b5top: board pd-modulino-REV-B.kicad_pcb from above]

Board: 2 copper layers, 41.0 x 25.4 mm, 37 parts (0 on the bottom side), 21 nets.

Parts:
C1, C2, C3, C4: 1.0u; C_0603_1608Metric
C6: 100n; C_0603_1608Metric
C7: 4.7u; C_0603_1608Metric
D1: ESDA25W; SOT65P210X110-3N
D2, D3, D4: ESDA25P35-1U1M; TVS_ESDA25P35-1U1M
D5: LED; LED_0603_1608Metric
J1: PRT-14417; CONN_PRT-14417_SPK
J2, J3: DX07S016JA1R1500; JAE_DX07S016JA1R1500
Q1, Q2: STL6P3LLH6; TRANS_STL6P3LLH6
R1, R2, R6: 10k; R_0603_1608Metric
R3, R4, R10: 100k; R_0603_1608Metric
R5: 330; R_0603_1608Metric
R5#2: 4.7k; R_0603_1608Metric
R7: 470; R_0603_1608Metric
R8, R11: 1k; R_0603_1608Metric
R9: 22k; R_0603_1608Metric
R12, R14, R15, R16: 5.1k; R_0603_1608Metric
R13: 100; R_0603_1608Metric
TP1: TestPoint; TestPoint_Pad_1.0x1.0mm
TP2: TestPoint; TestPoint_Loop_D2.60mm_Drill1.6mm_Beaded
U1: STUSB4500QTR
e1: 4.7k; R_0603_1608Metric

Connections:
/Power Subsystem/2V7: C1.2, C2.2, C3.2, Q1.1, Q1.2, Q1.3, Q2.1, Q2.2, Q2.3, R1.2, R2.2, R10.2, U1.21 (VREG_1V2), U1.23 (VREG_2V7), U1.24 (VDD)
/Power Subsystem/D+: J2.6 (D+), J2.7 (D+__1), J3.6 (D+), J3.7 (D+__1)
/Power Subsystem/D-: J2.5 (D-), J2.8 (D-__1), J3.5 (D-), J3.8 (D-__1)
/Power Subsystem/SCL: J1.4, U1.7 (SCL), e1.2
/Power Subsystem/SDA: J1.3, R5#2.2, U1.8 (SDA)
/Power Subsystem/USB_CC1: D1.2, J2.3 (CC1), J3.3 (CC1), R12.1, R14.1, U1.1 (CC1DB), U1.2 (CC1)
/Power Subsystem/USB_CC2: D1.1, J2.9 (CC2), J3.9 (CC2), R15.1, R16.1, U1.4 (CC2), U1.5 (CC2DB)
/Power Subsystem/USB_VBUS: C7.1, D2.A, D3.C, J3.2 (VBUS), J3.11 (VBUS__1), Q1.5_8, R7.2
/Power Subsystem/VBUS_VS_DISCH: R8.1, U1.18 (VBUS_VS_DISCH)
/Power Subsystem/Vsink: C6.2, D4.C, D5.2 (A), J2.2 (VBUS), J2.11 (VBUS__1), Q2.5_8, R11.1, TP2.1
GND: C1.1, C2.1, C3.1, C4.2, C7.2, D1.3, D3.A, D4.A, J1.1, J2.1 (GND), J2.12 (GND__1), J2.S1 (SHIELD), J2.S2 (SHIELD__1), J2.S3 (SHIELD__2), J2.S4 (SHIELD__3), J2.S5 (SHIELD__4), J2.S6 (SHIELD__5), J3.1 (GND), J3.12 (GND__1), J3.S1 (SHIELD), J3.S2 (SHIELD__1), J3.S3 (SHIELD__2), J3.S4 (SHIELD__3), J3.S5 (SHIELD__4), J3.S6 (SHIELD__5), R3.1, R4.1, R5.2, R6.1, R12.2, R14.2, R15.2, R16.2, U1.10 (GND), U1.22 (VSYS), U1.25
unnamed: C4.1, D2.C, R7.1, R8.2
unnamed: C6.1, R13.1
unnamed: D5.1 (K), R5.1
unnamed: Q1.4, Q2.4, R9.2, R10.1, R13.2
unnamed: R5#2.1, TP1.1, e1.1
unnamed: R1.1, R3.2, R4.2, U1.12 (ADDR0)
unnamed: R2.1, U1.13 (ADDR1)
unnamed: R11.2, U1.9 (DISCH)
unnamed: R6.2, U1.6 (RESET)
unnamed: R9.1, U1.16 (VBUS_EN_SNK)

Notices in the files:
parts and their libraries:
As far as I know the LaunchPad rocket is released by TI under the Creative Commons license.
